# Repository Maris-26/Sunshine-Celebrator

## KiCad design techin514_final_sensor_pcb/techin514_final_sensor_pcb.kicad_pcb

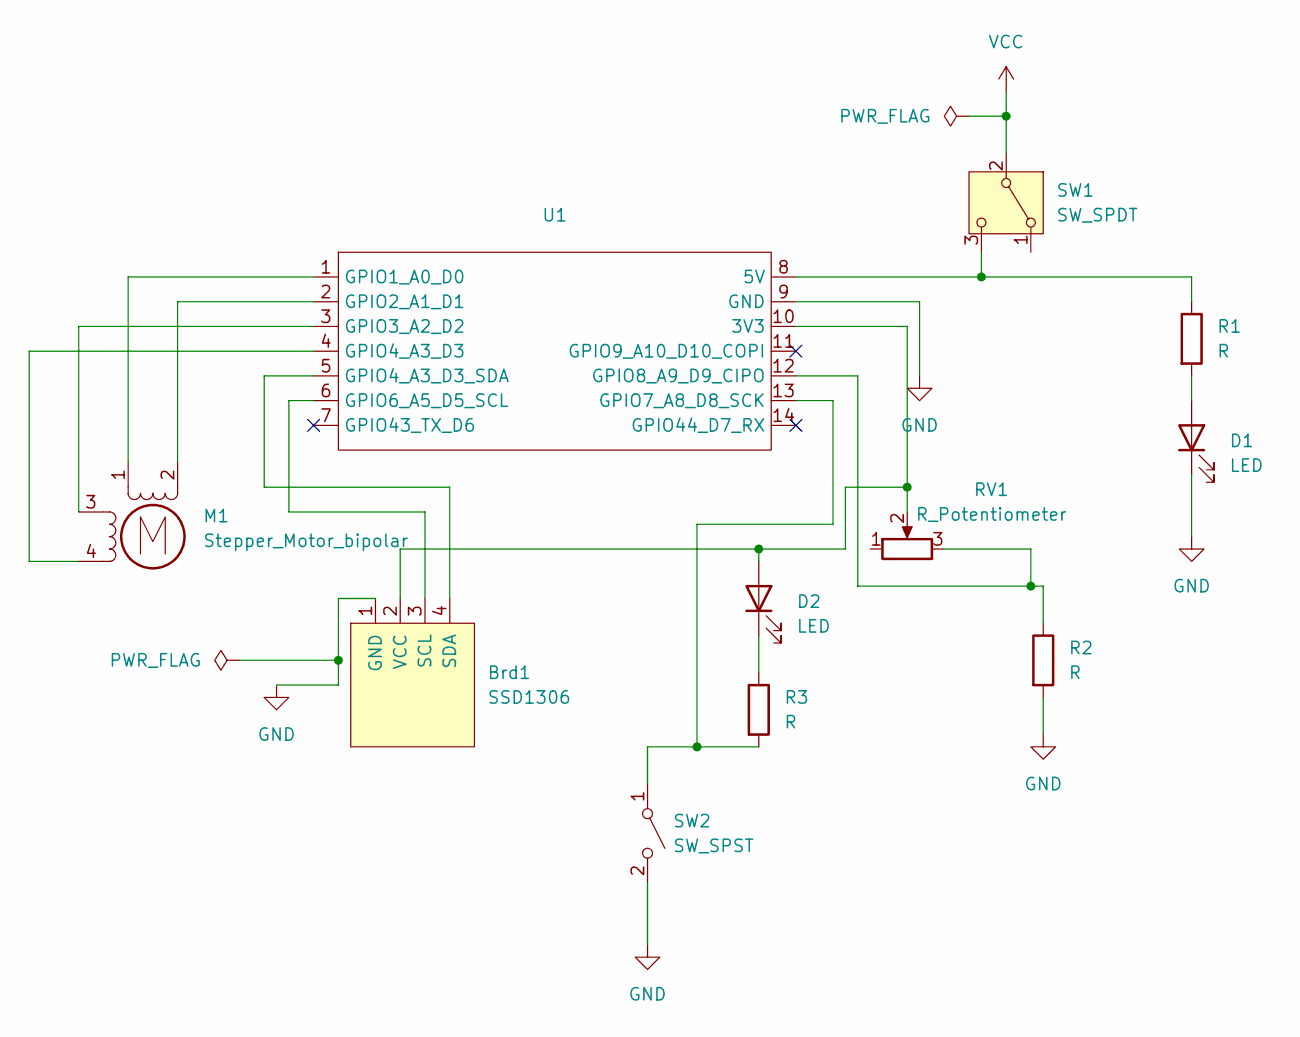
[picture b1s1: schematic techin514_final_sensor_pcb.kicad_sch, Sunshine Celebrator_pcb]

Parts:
Brd1: SSD1306; 128x64OLED
D1, D2: LED; LED_0805_2012Metric_Pad1.15x1.40mm_HandSolder
M1: Stepper_Motor_bipolar; x27_stepper
R1, R2, R3: R; R_0805_2012Metric_Pad1.20x1.40mm_HandSolder
RV1: R_Potentiometer; Potentiometer_Piher_PC-16_Single_Horizontal
SW1: SW_SPDT; JST_EH_B3B-EH-A_1x03_P2.50mm_Vertical
SW2: SW_SPST; SW_PUSH-12mm
U1: XIAO_ESP32_SENSE

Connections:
GND: Brd1.1 (GND), D1.1 (K), R2.2, SW2.2 (B), U1.9 (GND)
unnamed: Brd1.3 (SCL), U1.6 (GPIO6_A5_D5_SCL)
unnamed: Brd1.4 (SDA), U1.5 (GPIO4_A3_D3_SDA)
unnamed: Brd1.2 (VCC), D2.2 (A), RV1.2, U1.10 (3V3)
unnamed: D1.2 (A), R1.2
unnamed: D2.1 (K), R3.1
unnamed: M1.2 (-), U1.2 (GPIO2_A1_D1)
unnamed: R1.1, SW1.3 (C), U1.8 (5V)
unnamed: R3.2, SW2.1 (A), U1.13 (GPIO7_A8_D8_SCK)
unnamed: M1.1, U1.1 (GPIO1_A0_D0)
unnamed: M1.3, U1.3 (GPIO3_A2_D2)
unnamed: M1.4, U1.4 (GPIO4_A3_D3)
unnamed: R2.1, RV1.3, U1.12 (GPIO8_A9_D9_CIPO)
VCC: SW1.2 (B)

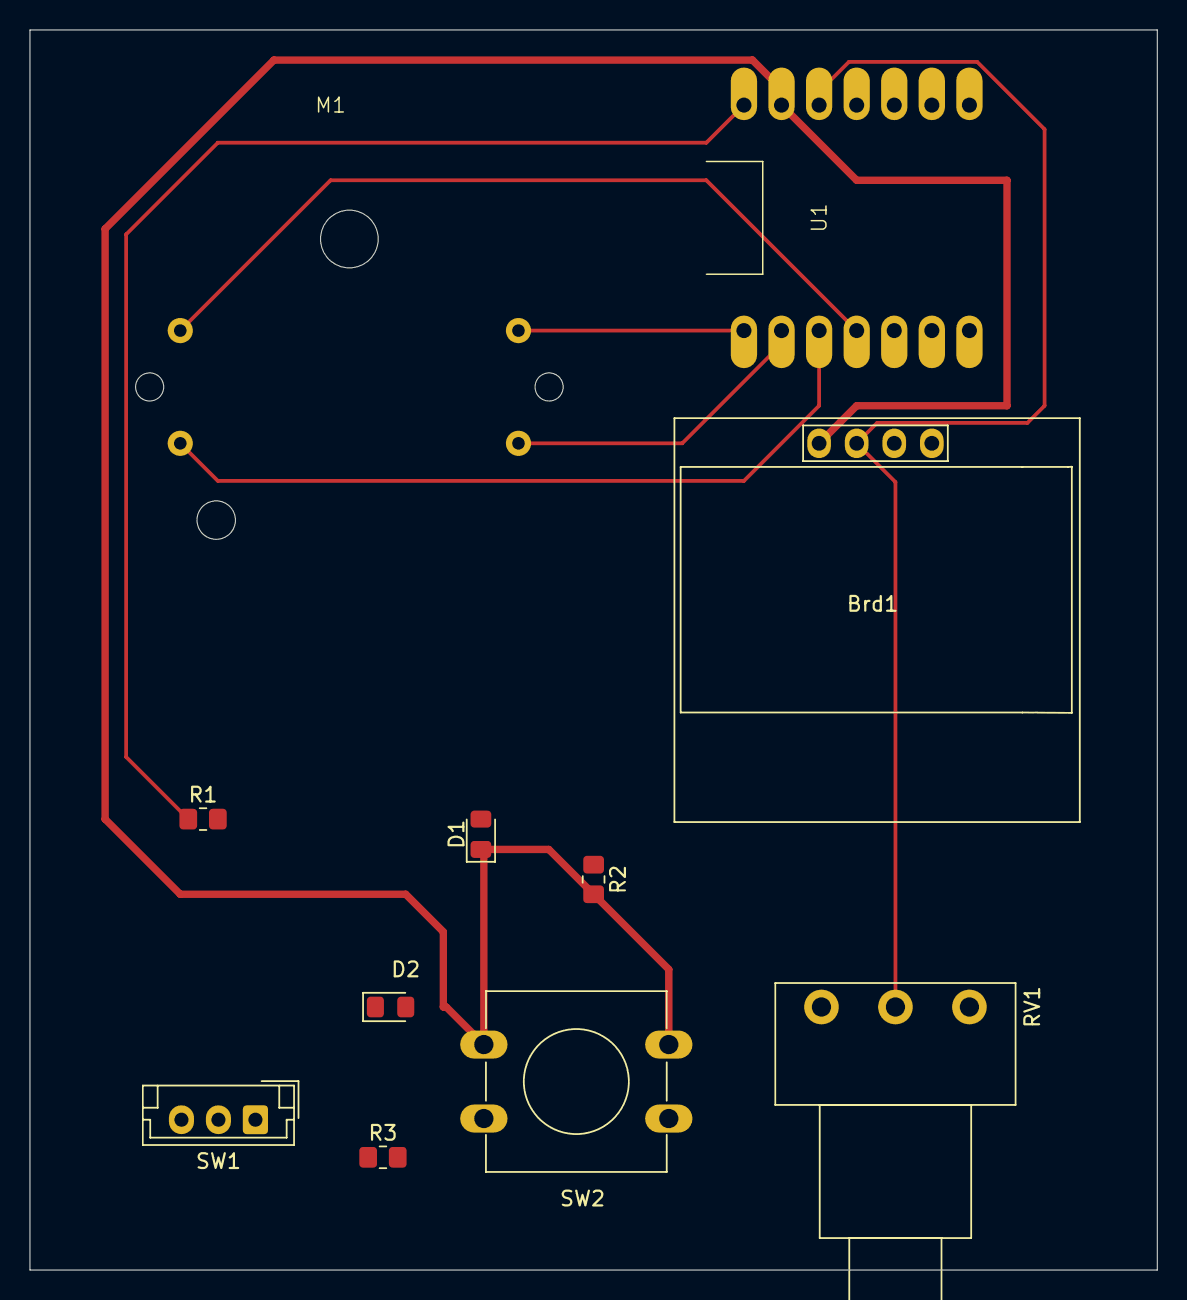
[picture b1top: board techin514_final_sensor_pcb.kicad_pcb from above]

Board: 2 copper layers, 76.2 x 83.8 mm, 11 parts (0 on the bottom side), 13 nets.

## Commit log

2025-01-22 Create datasheets
2025-01-22 datasheet file
2025-01-23 Create apds9960
2025-01-23 Update apds9960
2025-01-29 Create a folder for techin514_final_sensor_pcb
2025-02-05 Create Battery Management Lab
2025-02-05 0204Battery Management Lab
2025-03-12 Server-code
    I wrote the code of server in Arduino, because it only works on Arduino rather than VScode.
2025-03-12 Client-code
    I wrote the code for the client esp32c3 because it was only able to control the step motor on VScode rather than Arduino.
2025-03-12 Successful videos
2025-03-14 Final presentation
    With a clear record of the whole final project. Same as what I submitted on Canvas on March 12.
